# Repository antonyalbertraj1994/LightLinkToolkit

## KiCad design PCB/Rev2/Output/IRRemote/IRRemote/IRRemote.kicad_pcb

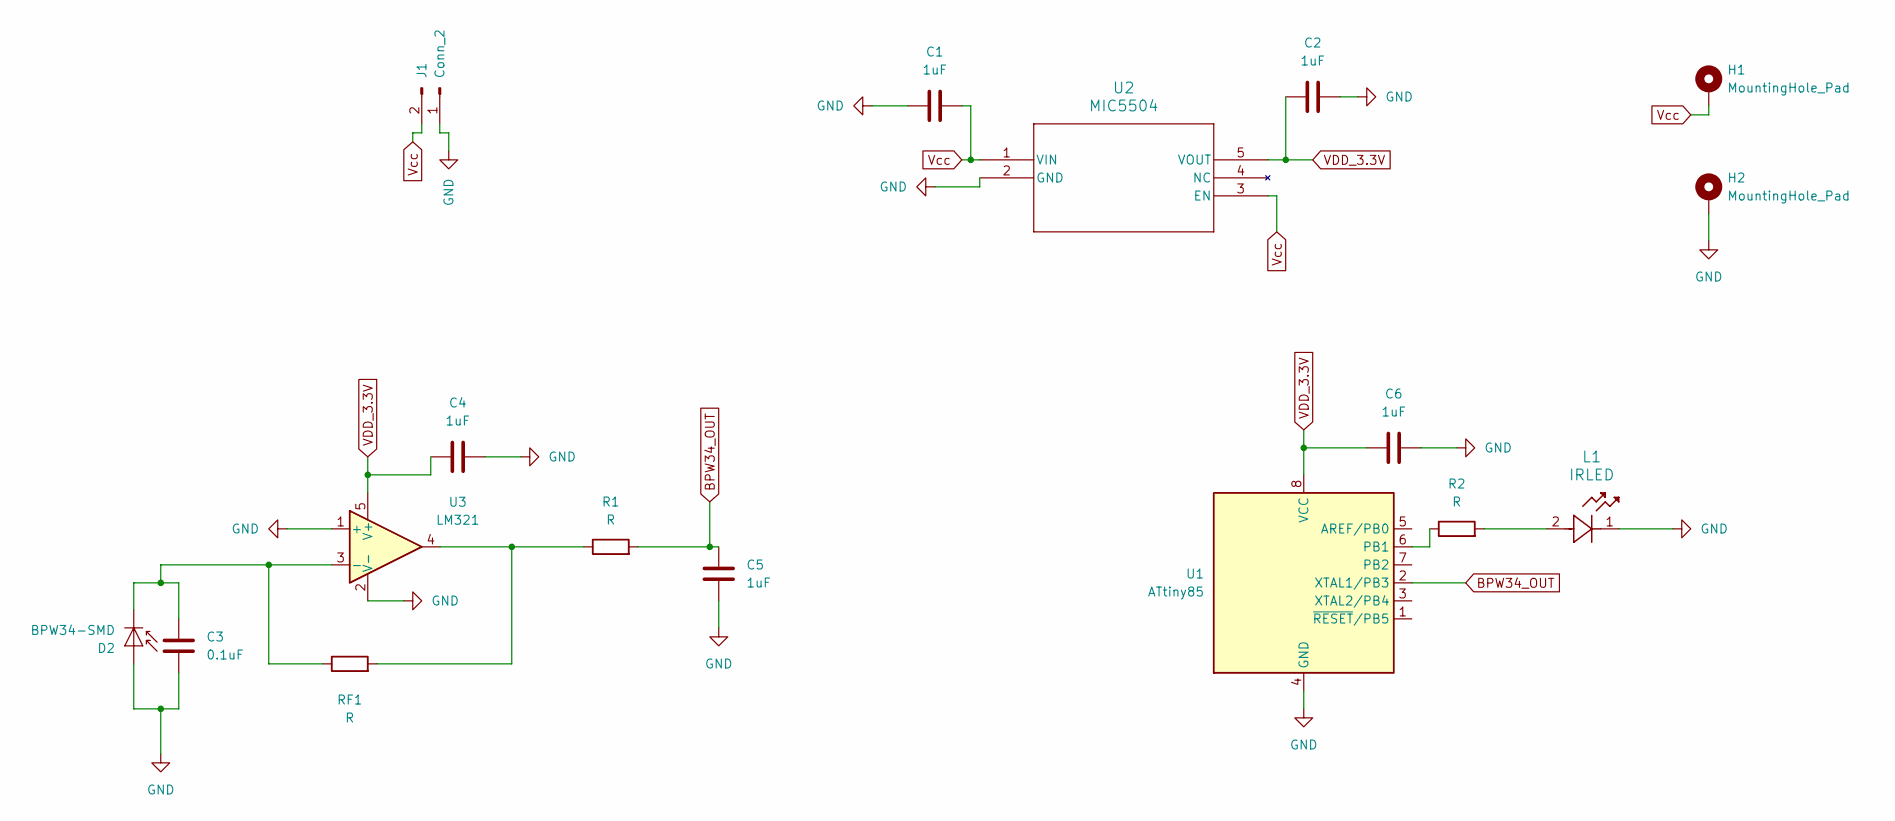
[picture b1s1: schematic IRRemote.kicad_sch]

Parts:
C1, C2, C4, C5, C6: 1uF; C_0603_1608Metric
C3: 0.1uF; C_0603_1608Metric
D2: BPW34-SMD; Osram_BPW34S-SMD
H1, H2: MountingHole_Pad; MT_Hole
J1: Conn_2; PinHeader_1x02_P2.54mm_Vertical
L1: IRLED; LED_IR12-21C&slash_TR8_EVE
R1, R2: R; R_0603_1608Metric
RF1: R; R_0603_1608Metric
U1: ATtiny85; SOIC-8W_5.3x5.3mm_P1.27mm
U2: MIC5504; SOT-23-5
U3: LM321; SOT-23-5

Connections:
BPW34_OUT: C5.2, R1.2, U1.2 (XTAL1/PB3)
GND: C1.1, C2.2, C3.1, C4.2, C5.1, C6.2, D2.2 (A), H2.1, J1.1, L1.1, U1.4 (GND), U2.2 (GND), U3.1 (+), U3.2 (V-)
unnamed: C3.2, D2.1 (K), RF1.1, U3.3 (-)
unnamed: L1.2, R2.2
unnamed: R1.1, RF1.2, U3.4
unnamed: R2.1, U1.6 (PB1)
VDD_3.3V: C2.1, C4.1, C6.1, U1.8 (VCC), U2.5 (VOUT), U3.5 (V+)
Vcc: C1.2, H1.1, J1.2, U2.1 (VIN), U2.3 (EN)

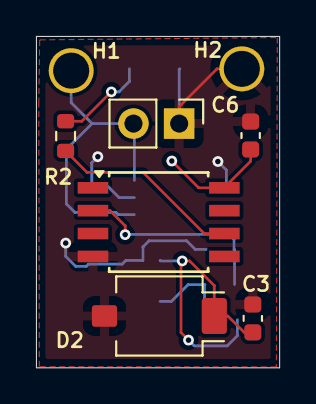
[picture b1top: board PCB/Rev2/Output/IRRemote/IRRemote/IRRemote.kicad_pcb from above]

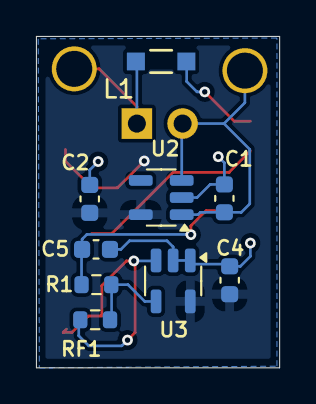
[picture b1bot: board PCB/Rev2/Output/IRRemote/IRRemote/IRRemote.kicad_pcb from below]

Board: 2 copper layers, 13.5 x 18.4 mm, 17 parts (9 on the bottom side), 8 nets.

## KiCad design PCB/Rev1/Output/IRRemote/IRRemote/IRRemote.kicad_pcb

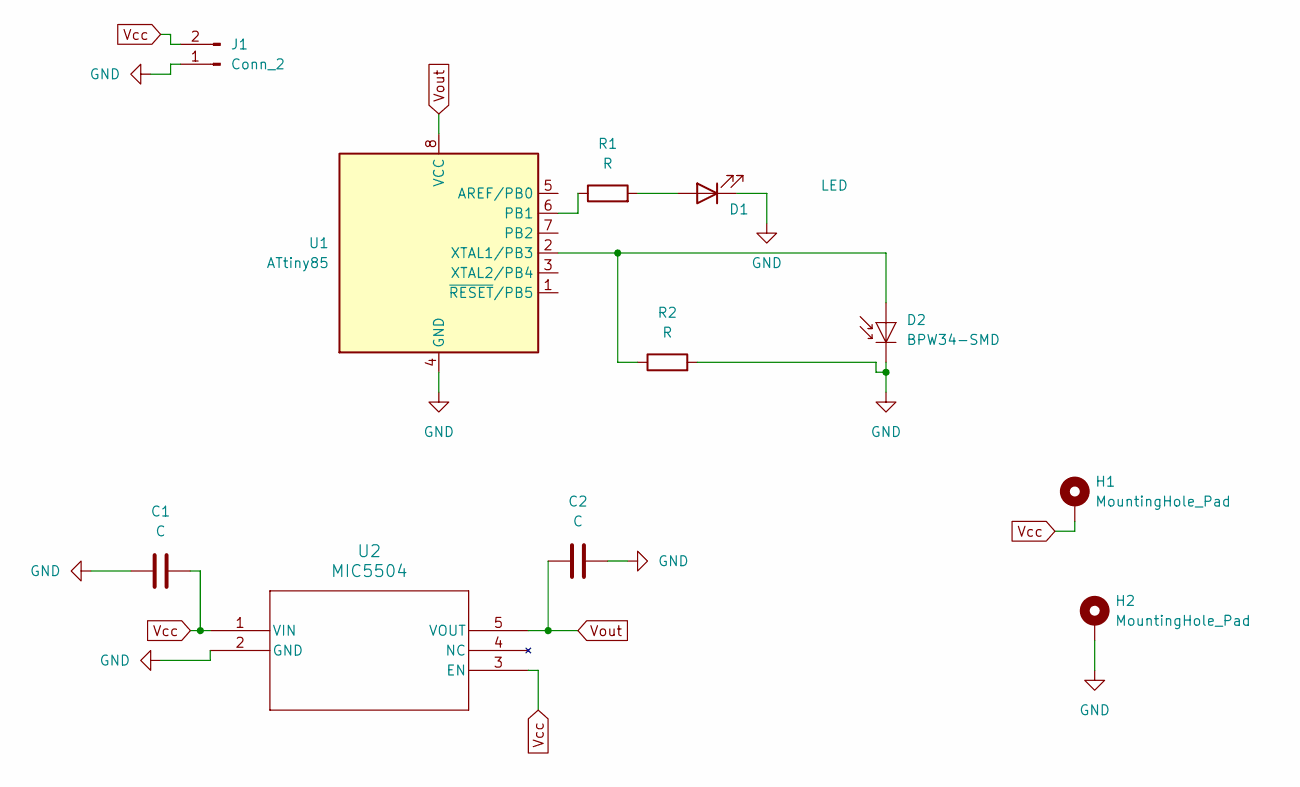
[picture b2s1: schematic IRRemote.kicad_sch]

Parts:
C1, C2: C; C_0603_1608Metric
D1: LED; LED_D5.0mm_Clear
D2: BPW34-SMD; Osram_BPW34S-SMD
H1, H2: MountingHole_Pad; MT_Hole
J1: Conn_2; PinHeader_1x02_P2.54mm_Vertical
R1: R; R_0603_1608Metric_Pad0.98x0.95mm_HandSolder
R2: R; R_0805_2012Metric
U1: ATtiny85; SOIC-8W_5.3x5.3mm_P1.27mm
U2: MIC5504; SOT-23-5

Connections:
GND: C1.1, C2.2, D1.1 (K), D2.1 (K), H2.1, J1.1, R2.2, U1.4 (GND), U2.2 (GND)
unnamed: D1.2 (A), R1.2
unnamed: D2.2 (A), R2.1, U1.2 (XTAL1/PB3)
unnamed: R1.1, U1.6 (PB1)
Vcc: C1.2, H1.1, J1.2, U2.1 (VIN), U2.3 (EN)
Vout: C2.1, U1.8 (VCC), U2.5 (VOUT)

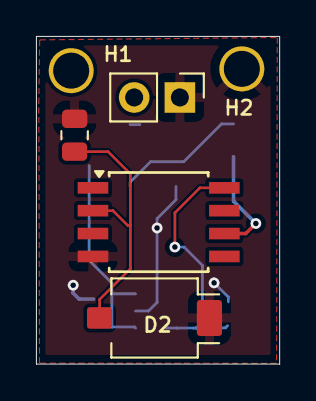
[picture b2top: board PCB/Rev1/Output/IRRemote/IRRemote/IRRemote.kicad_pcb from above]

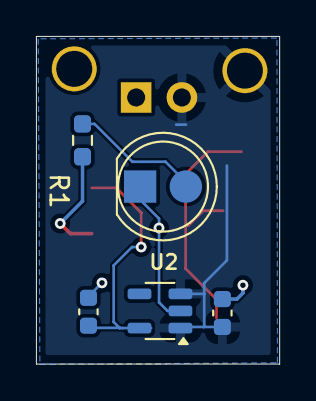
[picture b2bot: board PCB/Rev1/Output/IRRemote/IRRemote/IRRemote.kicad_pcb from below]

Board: 2 copper layers, 13.5 x 18.2 mm, 11 parts (5 on the bottom side), 6 nets.

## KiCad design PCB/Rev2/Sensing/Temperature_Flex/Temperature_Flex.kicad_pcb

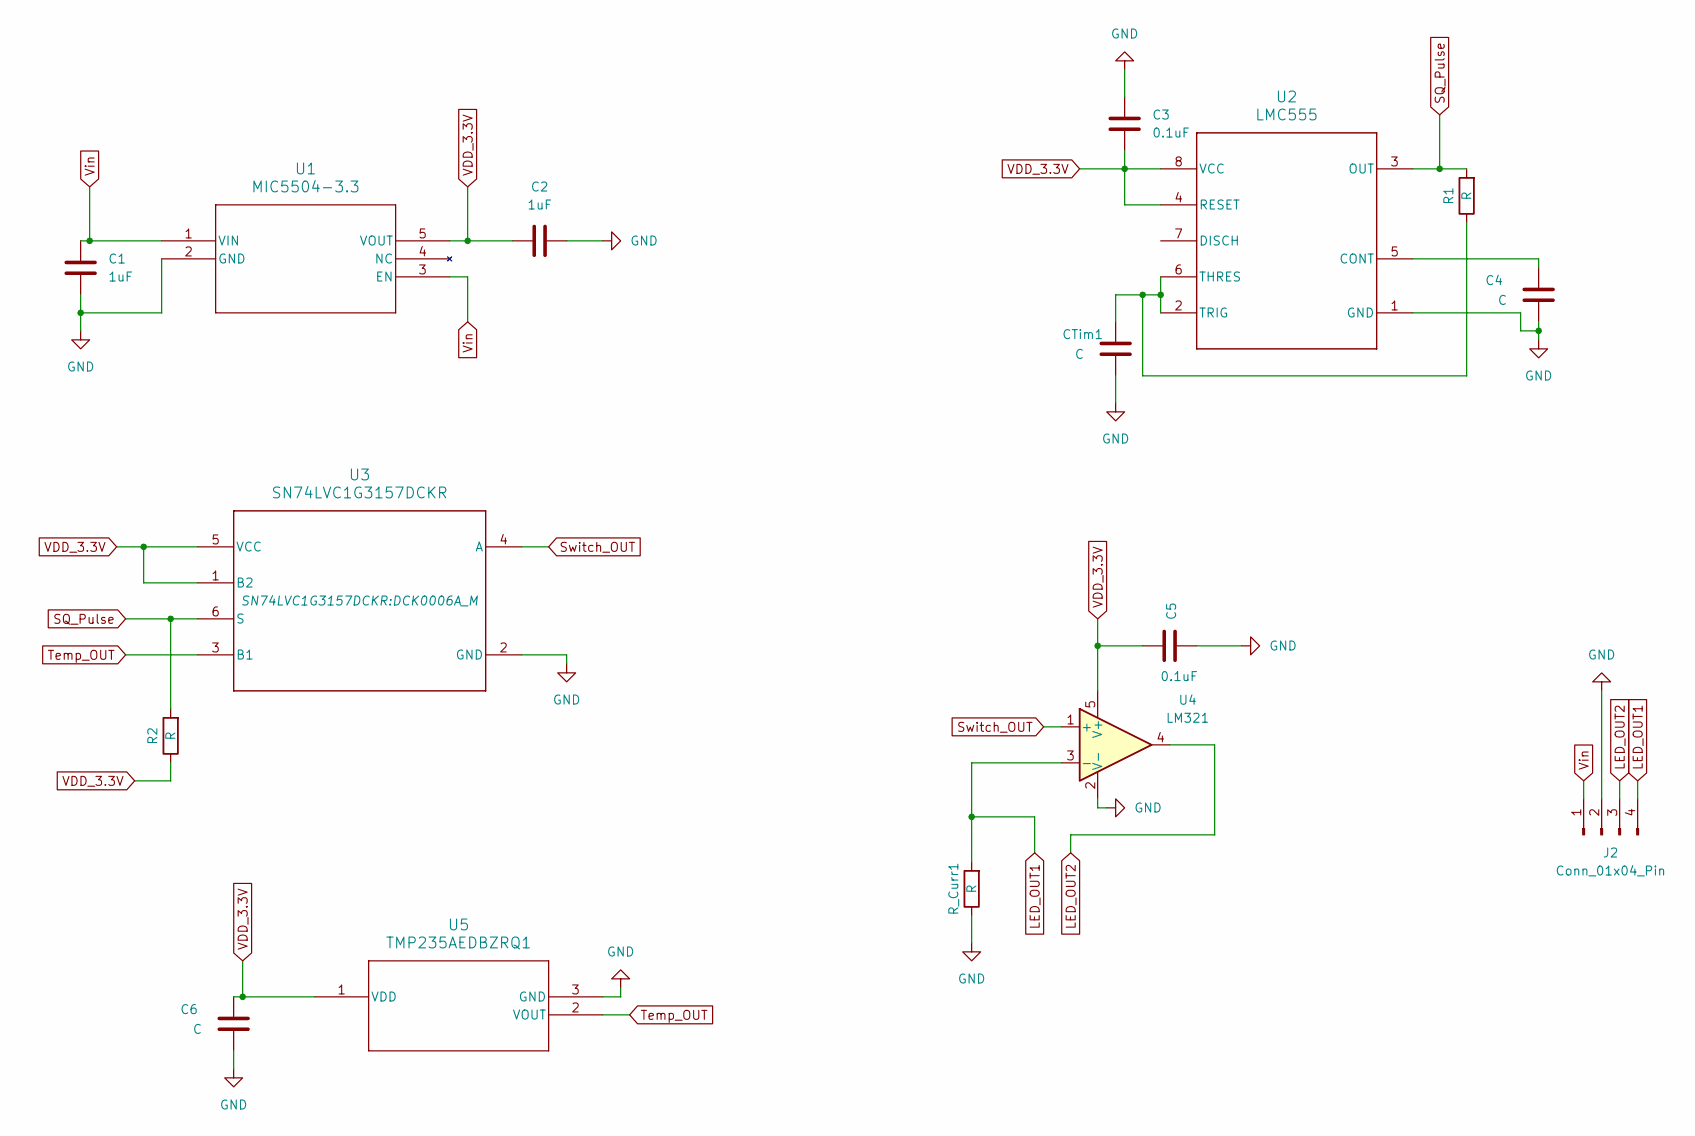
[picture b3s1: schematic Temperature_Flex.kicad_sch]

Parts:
C1, C2: 1uF; C_0603_1608Metric
C3, C5: 0.1uF; C_0603_1608Metric
C4, C6: C; C_0603_1608Metric
CTim1: C; C_0603_1608Metric
J2: Conn_01x04_Pin; PinHeader_1x04_P2.54mm_Vertical
R1, R2: R; R_0603_1608Metric
R_Curr1: R; R_0603_1608Metric
U1: MIC5504-3.3; SOT-23-5_MC_MCH
U2: LMC555; D0008A_M
U3: SN74LVC1G3157DCKR; DCK0006A_M
U4: LM321; SOT-23-5
U5: TMP235AEDBZRQ1; SOT-23_DBZ_TEX-M

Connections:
GND: C1.2, C2.2, C3.2, C4.1, C5.1, C6.1, CTim1.1, J2.2, R_Curr1.1, U1.2 (GND), U2.1 (GND), U3.2 (GND), U4.2 (V-), U5.3 (GND)
LED_OUT1: J2.4, R_Curr1.2, U4.3 (-)
LED_OUT2: J2.3, U4.4
unnamed: C4.2, U2.5 (CONT)
unnamed: CTim1.2, R1.1, U2.2 (TRIG), U2.6 (THRES)
SQ_Pulse: R1.2, R2.2, U2.3 (OUT), U3.6 (S)
Switch_OUT: U3.4 (A), U4.1 (+)
Temp_OUT: U3.3 (B1), U5.2 (VOUT)
VDD_3.3V: C2.1, C3.1, C5.2, C6.2, R2.1, U1.5 (VOUT), U2.4 (RESET), U2.8 (VCC), U3.1 (B2), U3.5 (VCC), U4.5 (V+), U5.1 (VDD)
Vin: C1.1, J2.1, U1.1 (VIN), U1.3 (EN)

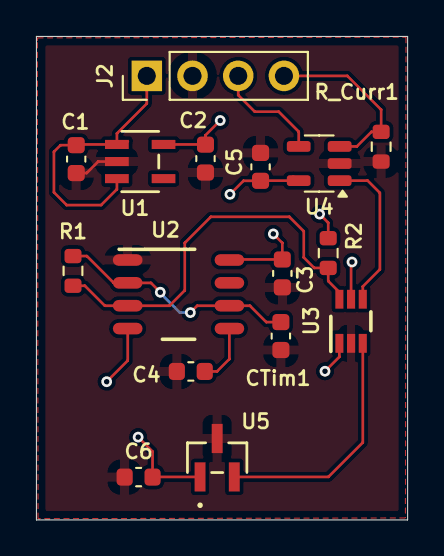
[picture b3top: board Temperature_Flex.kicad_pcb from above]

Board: 2 copper layers, 20.6 x 26.9 mm, 16 parts (0 on the bottom side), 10 nets.

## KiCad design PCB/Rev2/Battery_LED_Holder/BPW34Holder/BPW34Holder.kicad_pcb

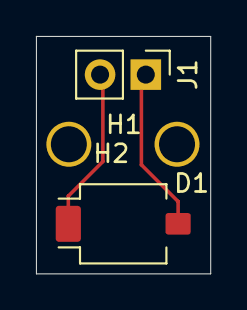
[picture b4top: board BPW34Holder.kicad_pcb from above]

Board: 2 copper layers, 9.7 x 13.2 mm, 4 parts (0 on the bottom side), 2 nets.

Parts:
D1: BPW34-SMD; Osram_BPW34S-SMD
H1, H2: MountingHole; MT_Hole
J1: Conn_01x02_Pin; PinHeader_1x02_P2.54mm_Vertical

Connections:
unnamed: D1.2 (A), J1.1
unnamed: D1.1 (K), J1.2

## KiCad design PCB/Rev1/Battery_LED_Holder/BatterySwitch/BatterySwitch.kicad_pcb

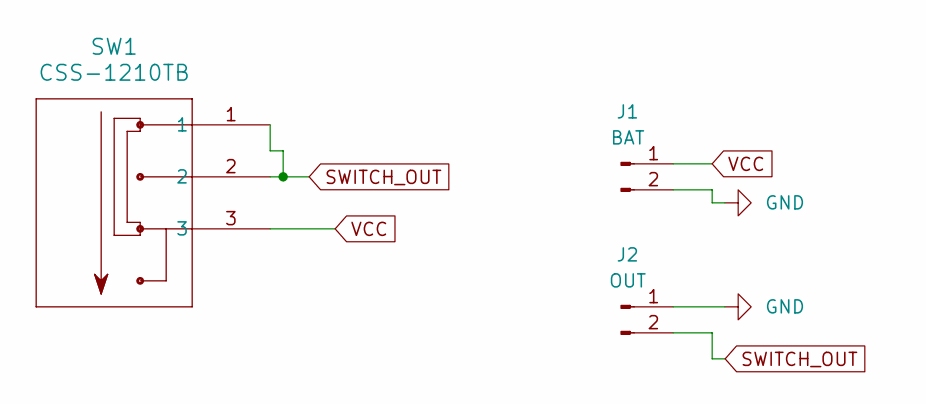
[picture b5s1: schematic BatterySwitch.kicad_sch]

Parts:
J1: BAT; PinHeader_1x02_P2.54mm_Vertical
J2: OUT; PinHeader_1x02_P2.54mm_Vertical
SW1: CSS-1210TB; SW3_CSS-1210TB_NDC

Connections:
GND: J1.2, J2.1
SWITCH_OUT: J2.2, SW1.1, SW1.2
VCC: J1.1, SW1.3

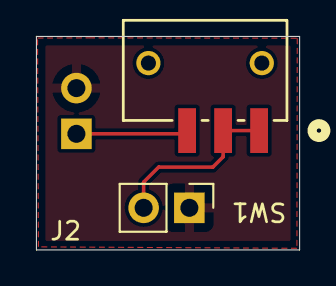
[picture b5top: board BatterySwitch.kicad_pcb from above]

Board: 2 copper layers, 14.6 x 11.9 mm, 3 parts (1 on the bottom side), 3 nets.

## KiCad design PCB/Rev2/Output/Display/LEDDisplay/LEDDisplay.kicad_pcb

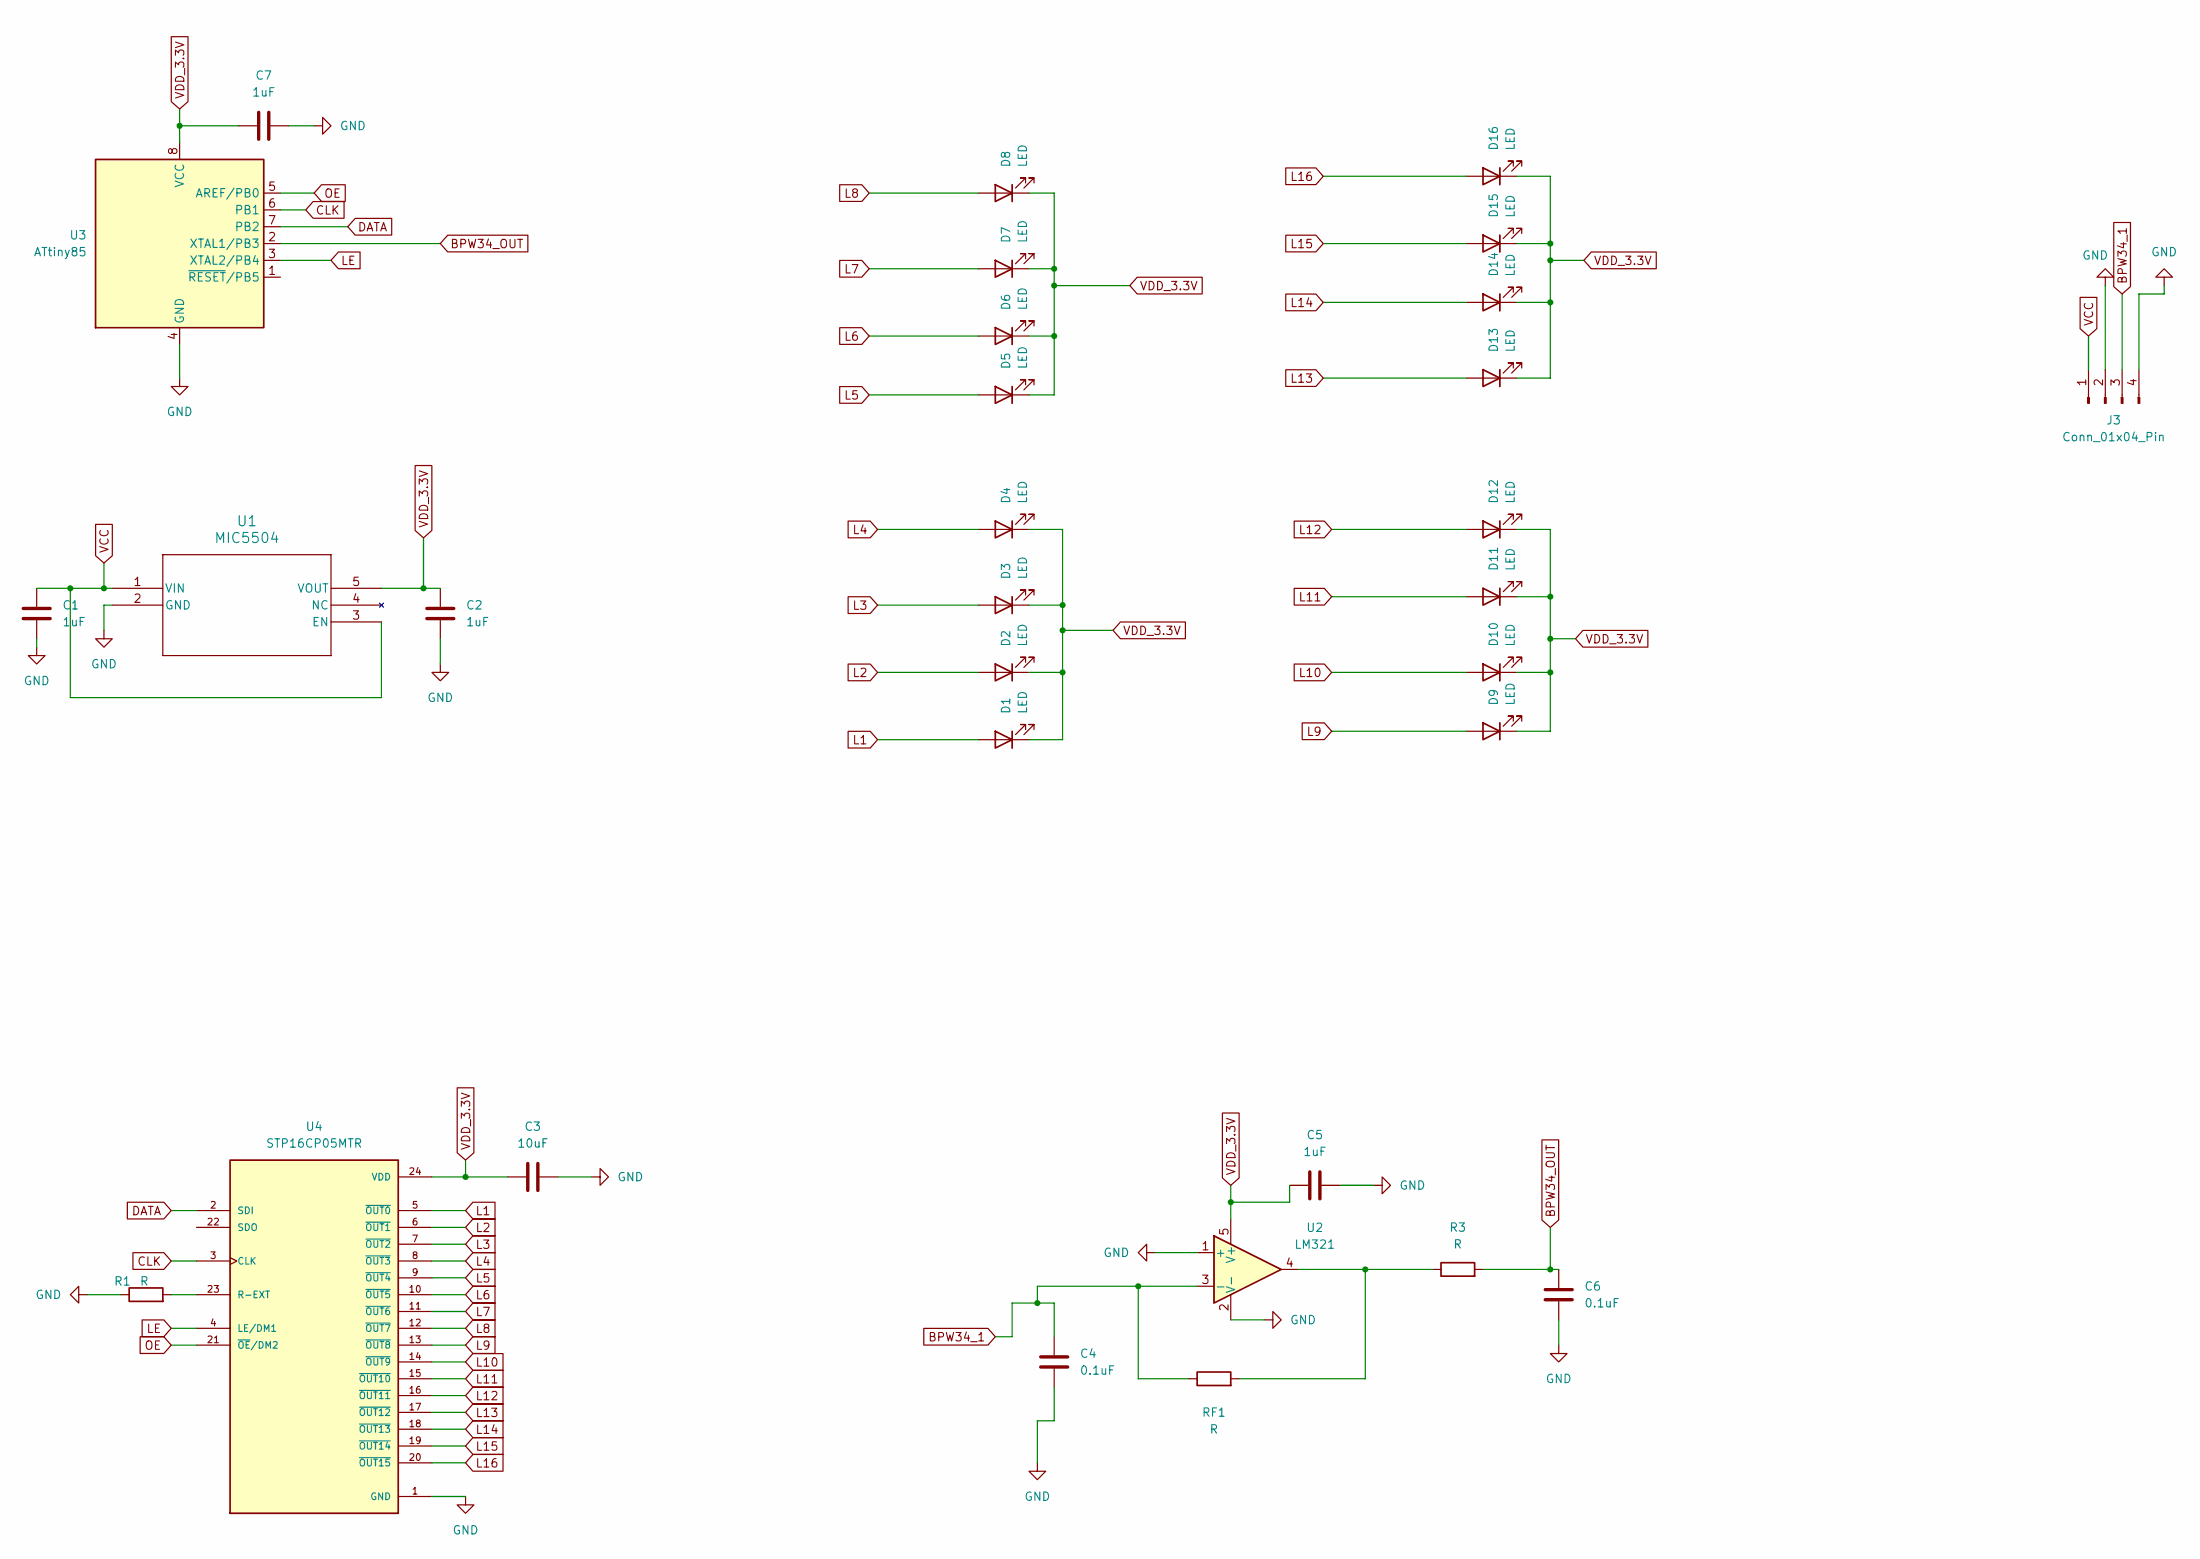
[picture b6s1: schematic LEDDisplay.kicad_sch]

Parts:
C1, C2: 1uF; C_0603_1608Metric_Pad1.08x0.95mm_HandSolder
C3: 10uF; C_0603_1608Metric_Pad1.08x0.95mm_HandSolder
C4, C6: 0.1uF; C_0603_1608Metric
C5, C7: 1uF; C_0603_1608Metric
D1, D2, D3, D4, D5, D6, D7, D8, D9, D10, D11, D12, D13, D14, D15, D16: LED; LED_0805_2012Metric_Pad1.15x1.40mm_HandSolder
J3: Conn_01x04_Pin; PinHeader_1x04_P2.54mm_Vertical
R1: R; R_0603_1608Metric_Pad0.98x0.95mm_HandSolder
R3: R; R_0603_1608Metric
RF1: R; R_0603_1608Metric
U1: MIC5504; SOT-23-5_MC_MCH
U2: LM321; SOT-23-5
U3: ATtiny85; SOIC-8W_5.3x5.3mm_P1.27mm
U4: STP16CP05MTR; SOIC127P1032X265-24N

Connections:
BPW34_1: C4.2, J3.3, RF1.1, U2.3 (-)
BPW34_OUT: C6.2, R3.2, U3.2 (XTAL1/PB3)
CLK: U3.6 (PB1), U4.3 (CLK)
DATA: U3.7 (PB2), U4.2 (SDI)
GND: C1.2, C2.2, C3.2, C4.1, C5.2, C6.1, C7.2, J3.2, J3.4, R1.1, U1.2 (GND), U2.1 (+), U2.2 (V-), U3.4 (GND), U4.1 (GND)
L1: D1.2 (A), U4.5 (~OUT0)
L2: D2.2 (A), U4.6 (~OUT1)
L3: D3.2 (A), U4.7 (~OUT2)
L4: D4.2 (A), U4.8 (~OUT3)
L5: D5.2 (A), U4.9 (~OUT4)
L6: D6.2 (A), U4.10 (~OUT5)
L7: D7.2 (A), U4.11 (~OUT6)
L8: D8.2 (A), U4.12 (~OUT7)
L9: D9.2 (A), U4.13 (~OUT8)
L10: D10.2 (A), U4.14 (~OUT9)
L11: D11.2 (A), U4.15 (~OUT10)
L12: D12.2 (A), U4.16 (~OUT11)
L13: D13.2 (A), U4.17 (~OUT12)
L14: D14.2 (A), U4.18 (~OUT13)
L15: D15.2 (A), U4.19 (~OUT14)
L16: D16.2 (A), U4.20 (~OUT15)
LE: U3.3 (XTAL2/PB4), U4.4 (LE/DM1)
unnamed: R3.1, RF1.2, U2.4
unnamed: R1.2, U4.23 (R-EXT)
OE: U3.5 (AREF/PB0), U4.21 (~OE/DM2)
VCC: C1.1, J3.1, U1.1 (VIN), U1.3 (EN)
VDD_3.3V: C2.1, C3.1, C5.1, C7.1, D1.1 (K), D2.1 (K), D3.1 (K), D4.1 (K), D5.1 (K), D6.1 (K), D7.1 (K), D8.1 (K), D9.1 (K), D10.1 (K), D11.1 (K), D12.1 (K), D13.1 (K), D14.1 (K), D15.1 (K), D16.1 (K), U1.5 (VOUT), U2.5 (V+), U3.8 (VCC), U4.24 (VDD)

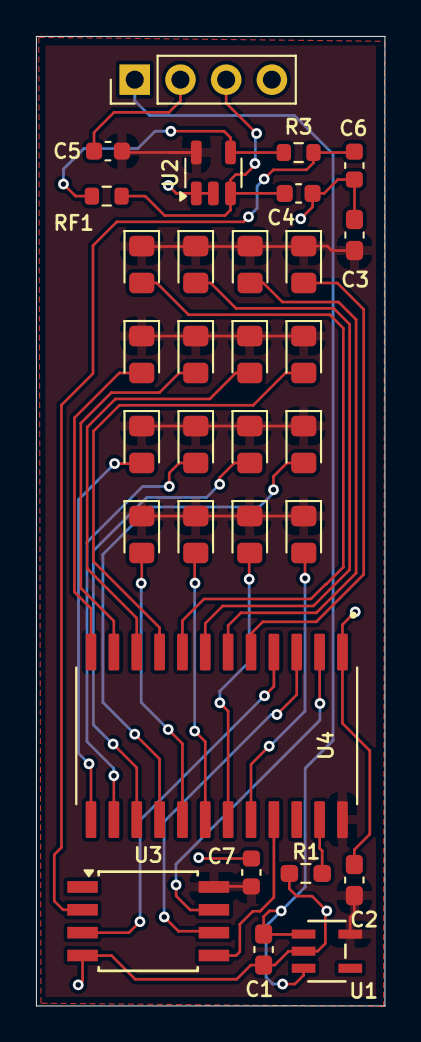
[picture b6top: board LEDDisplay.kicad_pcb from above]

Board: 2 copper layers, 19.4 x 53.9 mm, 31 parts (0 on the bottom side), 27 nets.

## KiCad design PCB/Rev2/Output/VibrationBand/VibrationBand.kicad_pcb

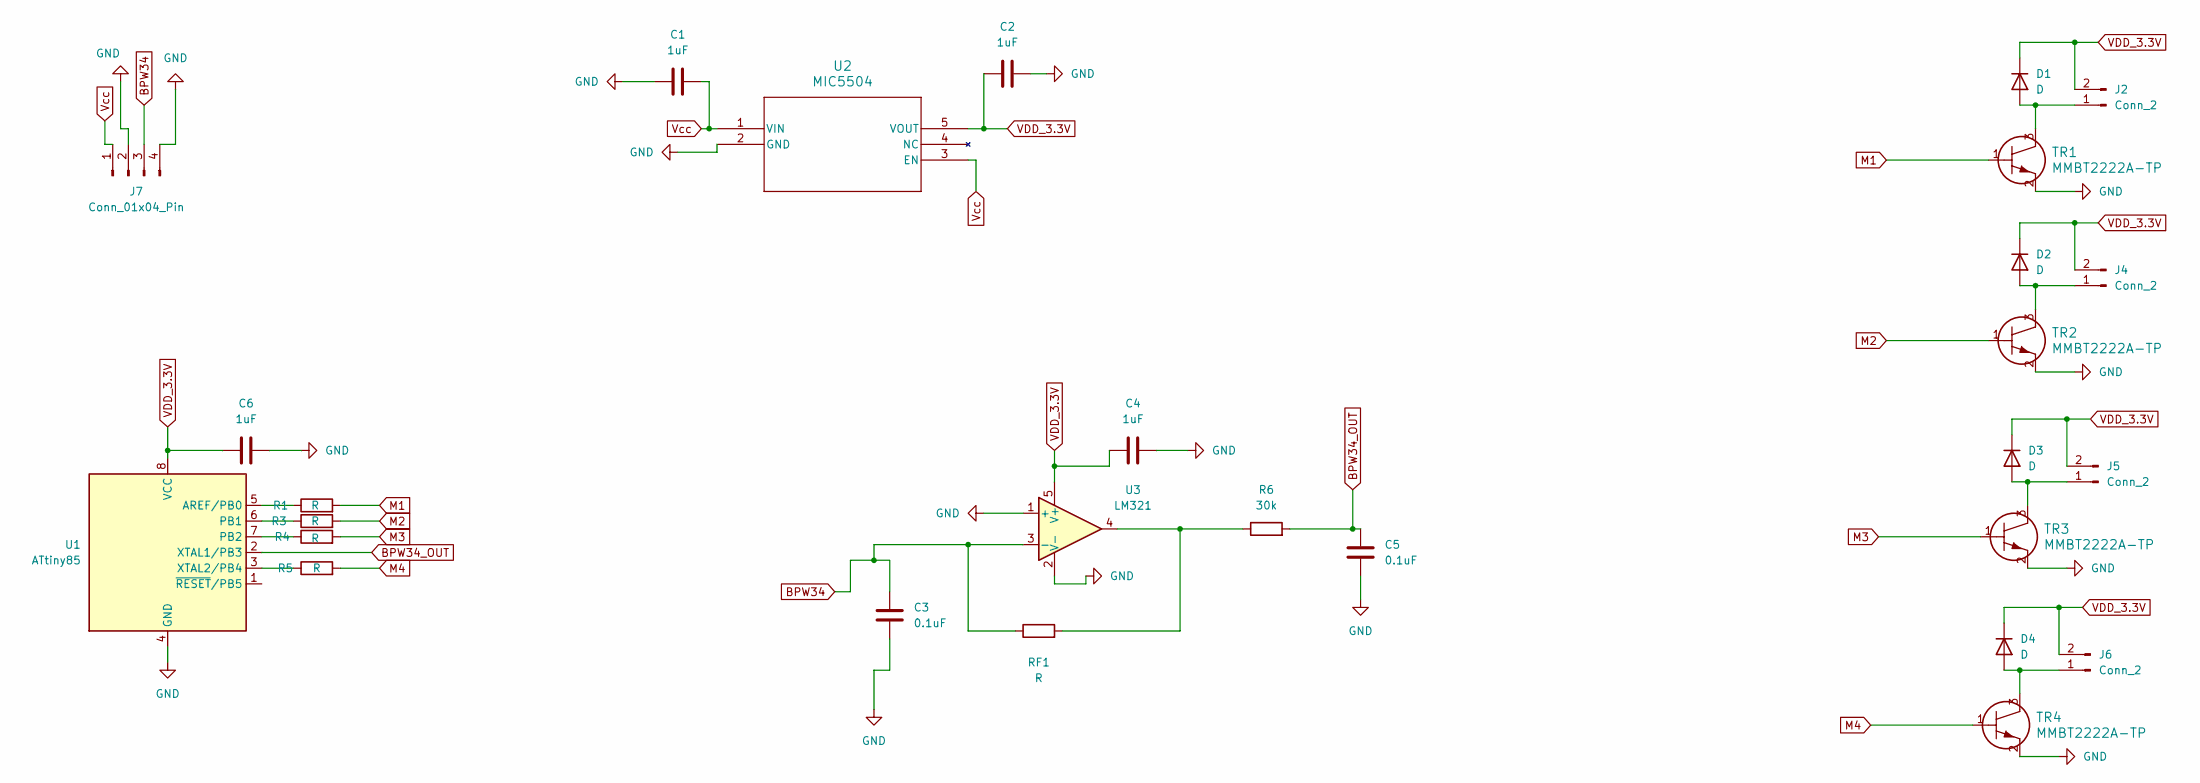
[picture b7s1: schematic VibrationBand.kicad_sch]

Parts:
C1, C2: 1uF; C_0603_1608Metric_Pad1.08x0.95mm_HandSolder
C3, C5: 0.1uF; C_0603_1608Metric
C4, C6: 1uF; C_0603_1608Metric
D1, D2, D3, D4: D; SOD123_DIO
J2, J4, J5, J6: Conn_2; PinHeader_1x02_P2.54mm_Vertical
J7: Conn_01x04_Pin; PinHeader_1x04_P2.54mm_Vertical
R1, R3, R4, R5: R; R_0603_1608Metric_Pad0.98x0.95mm_HandSolder
R6: 30k; R_0603_1608Metric
RF1: R; R_0603_1608Metric
TR1, TR2, TR3, TR4: MMBT2222A-TP; MTR_MMBT2222A-TP_MCE
U1: ATtiny85; SOIC-8W_5.3x5.3mm_P1.27mm
U2: MIC5504; SOT-23-5
U3: LM321; SOT-23-5

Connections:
BPW34: C3.2, J7.3, RF1.1, U3.3 (-)
BPW34_OUT: C5.2, R6.2, U1.2 (XTAL1/PB3)
GND: C1.1, C2.2, C3.1, C4.2, C5.1, C6.1, J7.2, J7.4, TR1.2, TR2.2, TR3.2, TR4.2, U1.4 (GND), U2.2 (GND), U3.1 (+), U3.2 (V-)
M1: R1.2, TR1.1
M2: R3.2, TR2.1
M3: R4.2, TR3.1
M4: R5.2, TR4.1
unnamed: D1.2 (A), J2.1, TR1.3
unnamed: D2.2 (A), J4.1, TR2.3
unnamed: D3.2 (A), J5.1, TR3.3
unnamed: D4.2 (A), J6.1, TR4.3
unnamed: R6.1, RF1.2, U3.4
unnamed: R1.1, U1.5 (AREF/PB0)
unnamed: R3.1, U1.6 (PB1)
unnamed: R4.1, U1.7 (PB2)
unnamed: R5.1, U1.3 (XTAL2/PB4)
VDD_3.3V: C2.1, C4.1, C6.2, D1.1 (K), D2.1 (K), D3.1 (K), D4.1 (K), J2.2, J4.2, J5.2, J6.2, U1.8 (VCC), U2.5 (VOUT), U3.5 (V+)
Vcc: C1.2, J7.1, U2.1 (VIN), U2.3 (EN)

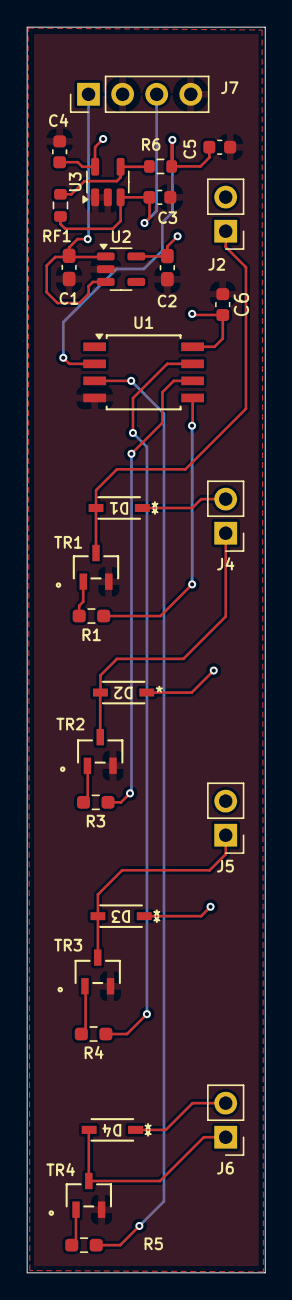
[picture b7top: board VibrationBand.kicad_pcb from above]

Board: 2 copper layers, 17.7 x 92.8 mm, 28 parts (0 on the bottom side), 18 nets.

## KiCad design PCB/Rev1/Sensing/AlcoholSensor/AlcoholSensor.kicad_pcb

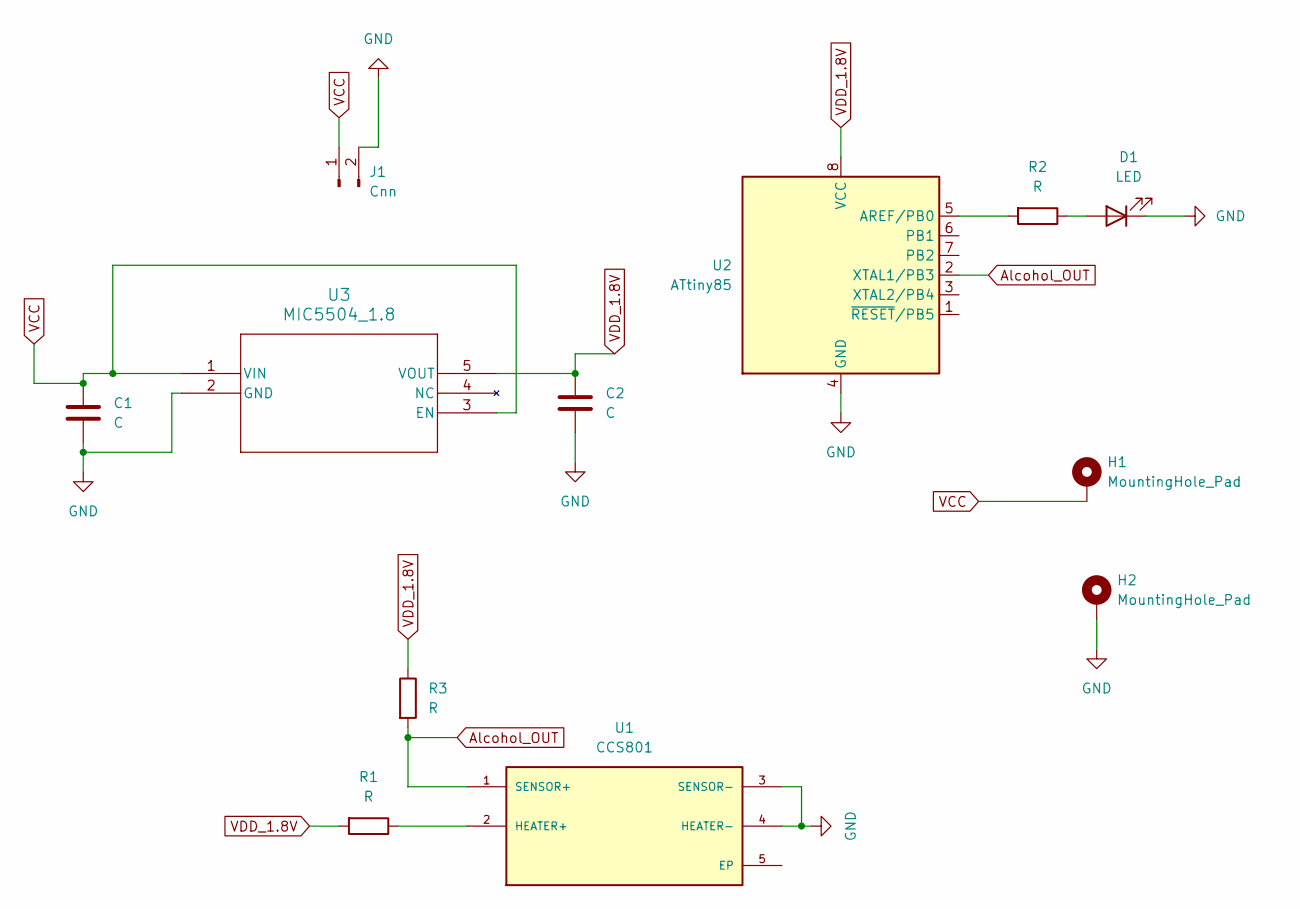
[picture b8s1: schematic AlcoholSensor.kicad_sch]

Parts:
C1, C2: C; C_0603_1608Metric_Pad1.08x0.95mm_HandSolder
D1: LED; LED_0805_2012Metric_Pad1.15x1.40mm_HandSolder
H1, H2: MountingHole_Pad; MT_Hole
J1: Cnn; PinHeader_1x02_P2.54mm_Vertical
R1, R2, R3: R; R_0603_1608Metric_Pad0.98x0.95mm_HandSolder
U1: CCS801; XDCR_CCS801; PARTREV v1-04
U2: ATtiny85; SOIC-8W_5.3x5.3mm_P1.27mm
U3: MIC5504_1.8; SOT23-5LD-PL-1_MCH

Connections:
Alcohol_OUT: R3.2, U1.1 (SENSOR+), U2.2 (XTAL1/PB3)
GND: C1.2, C2.2, D1.1 (K), H2.1, J1.2, U1.3 (SENSOR-), U1.4 (HEATER-), U2.4 (GND), U3.2 (GND)
unnamed: D1.2 (A), R2.1
unnamed: R1.1, U1.2 (HEATER+)
unnamed: R2.2, U2.5 (AREF/PB0)
VCC: C1.1, H1.1, J1.1, U3.1 (VIN), U3.3 (EN)
VDD_1.8V: C2.1, R1.2, R3.1, U2.8 (VCC), U3.5 (VOUT)

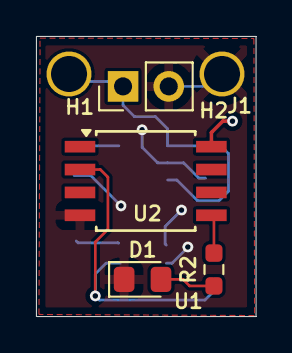
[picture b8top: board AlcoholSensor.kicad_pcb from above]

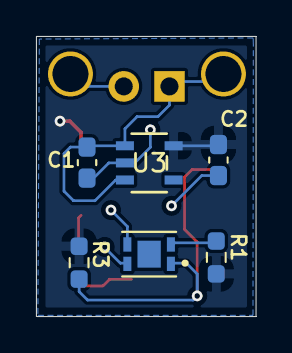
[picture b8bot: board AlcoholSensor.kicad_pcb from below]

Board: 2 copper layers, 12.2 x 15.6 mm, 12 parts (6 on the bottom side), 7 nets.

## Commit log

2025-04-04 InitialCommit
2025-04-04 Removed old Lightlink output
2025-04-04 Added new lightoutput study
2025-04-10 UIST deadline commit
2025-04-10 Changed speed
2025-07-10 UIST
